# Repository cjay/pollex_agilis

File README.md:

pollex_agilis
=============

Split ergonomic keyboard with many thumb keys.

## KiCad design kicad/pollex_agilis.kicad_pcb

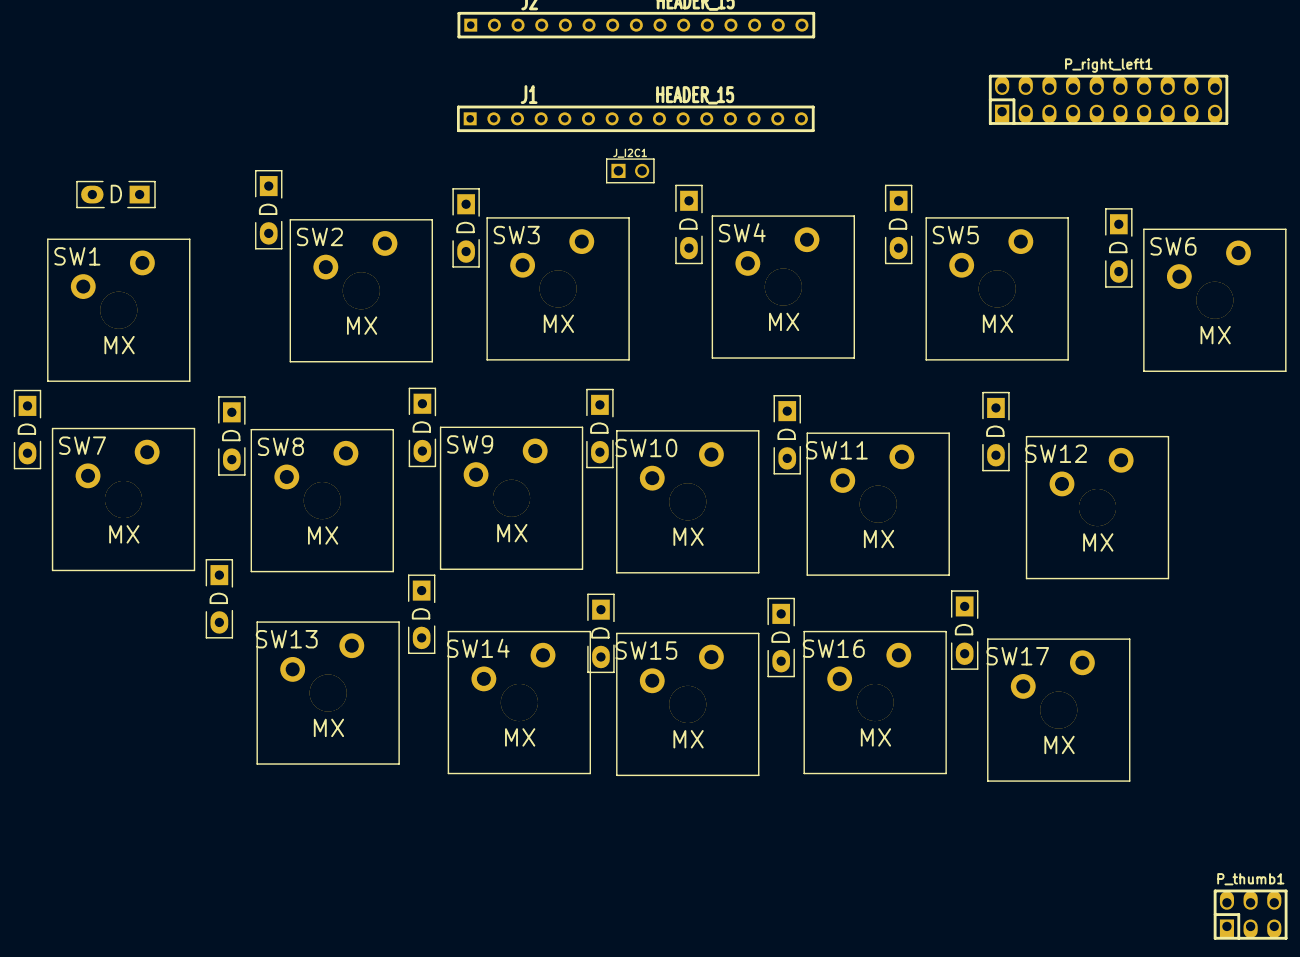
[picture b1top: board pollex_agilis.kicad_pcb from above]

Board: 2 copper layers, 39 parts (0 on the bottom side), 39 nets, no tracks yet.

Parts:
D1, D2, D3, D4, D5, D6, D7, D8, D9, D10, D11, D12, D13, D14, D15, D16, D17: D
J1, J2: HEADER_15; SIL-15
J_I2C1: HEADER_2; PIN_ARRAY_2X1
P_right_left1: CONN_10X2; pin_strip_10x2
P_thumb1: CONN_3X2; pin_strip_3x2
SW1, SW2, SW3, SW4, SW5, SW6, SW7, SW8, SW9, SW10, SW11, SW12, SW13, SW14, SW15, SW16, SW17: MX; SW_PLT_2PIN

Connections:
/B0: J1.3, SW1.1, SW7.1
/B1: J1.4, SW2.1, SW8.1, SW13.1
/B2: J1.5, SW3.1, SW9.1, SW14.1
/B3: J1.6, P_thumb1.5, SW4.1, SW10.1, SW15.1
/B4: J2.14, P_thumb1.3, SW5.1, SW11.1, SW16.1
/B5: J2.13, P_thumb1.1, SW6.1, SW12.1, SW17.1
/B6: J2.12, P_right_left1.1
/B7: J2.11, P_right_left1.3
/D0: J1.7, J_I2C1.1
/D1: J1.8, J_I2C1.2
/D2: D1.2, D2.2, D3.2, D4.2, D5.2, D6.2, J1.9, P_right_left1.2
/D3: D7.2, D8.2, D9.2, D10.2, D11.2, D12.2, J1.10, P_right_left1.4
/D4: D13.2, D14.2, D15.2, D16.2, D17.2, J1.11, P_right_left1.6
/D5: J1.12, P_right_left1.8, P_thumb1.2
/D6: J1.13, P_right_left1.10, P_thumb1.4
/D7: J1.14, P_right_left1.12, P_thumb1.6
/F0: J2.3, P_right_left1.5
/F1: J2.4, P_right_left1.7
/F4: J2.5, P_right_left1.9
/F5: J2.6, P_right_left1.11
/F6: J2.7, P_right_left1.13
GND: J1.15, J2.2, J2.15
unnamed: D17.1, SW17.2
unnamed: D16.1, SW16.2
unnamed: D15.1, SW15.2
unnamed: D8.1, SW8.2
unnamed: D10.1, SW10.2
unnamed: D9.1, SW9.2
unnamed: D7.1, SW7.2
unnamed: D6.1, SW6.2
unnamed: D14.1, SW14.2
unnamed: D13.1, SW13.2
unnamed: D12.1, SW12.2
unnamed: D11.1, SW11.2
unnamed: D1.1, SW1.2
unnamed: D5.1, SW5.2
unnamed: D4.1, SW4.2
unnamed: D3.1, SW3.2
unnamed: D2.1, SW2.2

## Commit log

2013-03-15 Test modification of readme
2013-03-15 removed x
2013-03-15 draft + empty kicad project
2013-03-15 schematics
    Schematics for left hand (without thumbkeys)
    * CherryMX library from key64 project
    * Connectors from W. Lain
2013-03-16 first layout + added connectors to thumb and right side board
    added footprints for the connectors
2013-03-16 added thumbboard and .brd file for older kicad versions
